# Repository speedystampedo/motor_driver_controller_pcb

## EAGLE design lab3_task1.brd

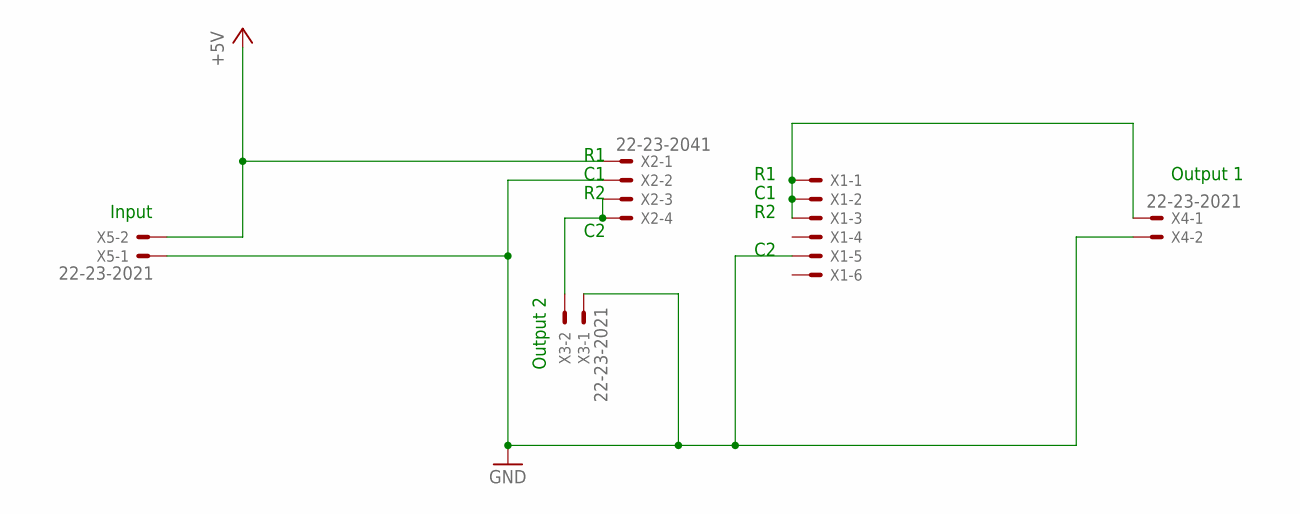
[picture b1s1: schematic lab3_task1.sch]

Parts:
X1: 22-23-2061
X2: 22-23-2041
X3, X4, X5: 22-23-2021

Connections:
+5V: X2.1, X5.2
GND: X1.5, X2.2, X3.1, X4.2, X5.1
unnamed: X1.1, X1.2, X1.3, X4.1
unnamed: X2.3, X2.4, X3.2

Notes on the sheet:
Output 1
Output 2
Input

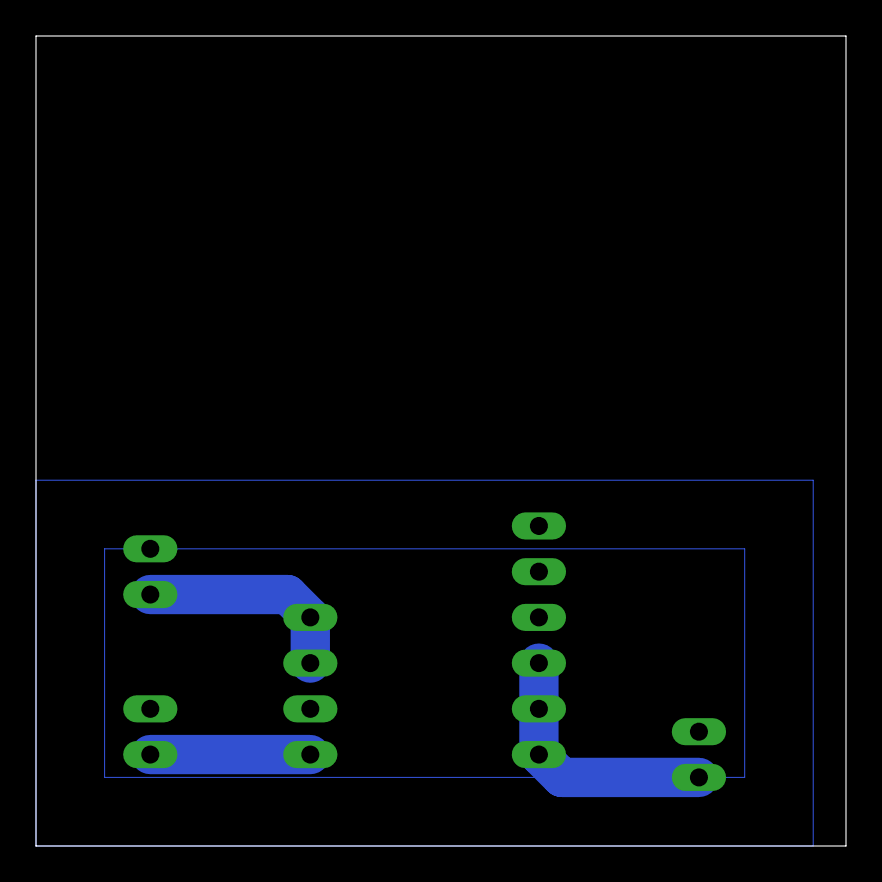
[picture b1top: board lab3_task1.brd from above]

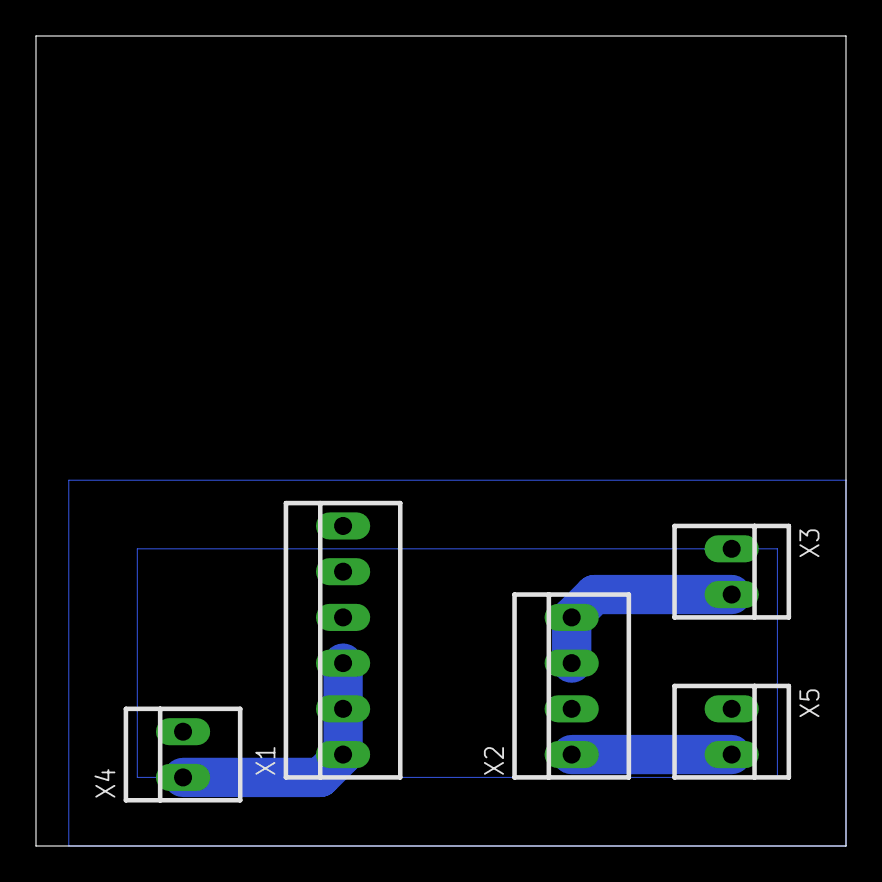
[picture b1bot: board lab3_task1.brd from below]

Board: 2 copper layers, 45.0 x 45.0 mm, 5 parts (5 on the bottom side), 4 nets.

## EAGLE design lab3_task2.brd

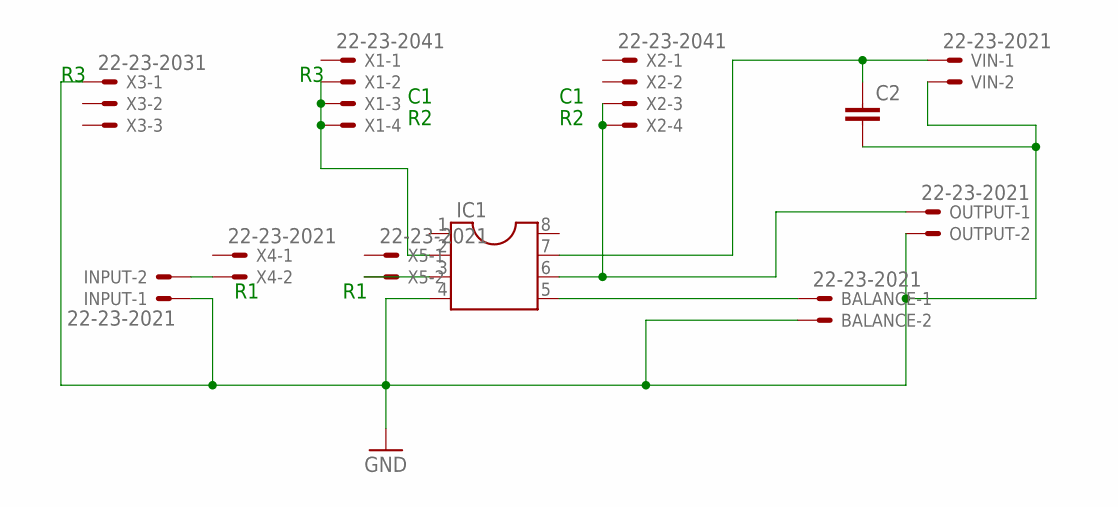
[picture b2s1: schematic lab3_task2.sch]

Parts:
BALANCE: 22-23-2021
C2: C-EU102-064X133; C102-064X133
IC1: DIL8; DIL08
INPUT: 22-23-2021
OUTPUT: 22-23-2021
VIN: 22-23-2021
X1, X2: 22-23-2041
X3: 22-23-2031
X4, X5: 22-23-2021

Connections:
GND: BALANCE.2, C2.2, IC1.4, INPUT.1, OUTPUT.2, VIN.2, X3.1
unnamed: INPUT.2, X4.2
unnamed: IC1.3, X5.2
unnamed: C2.1, IC1.7, VIN.1
unnamed: BALANCE.1, IC1.5
unnamed: IC1.6, OUTPUT.1, X2.3, X2.4
unnamed: IC1.2, X1.2, X1.3, X1.4

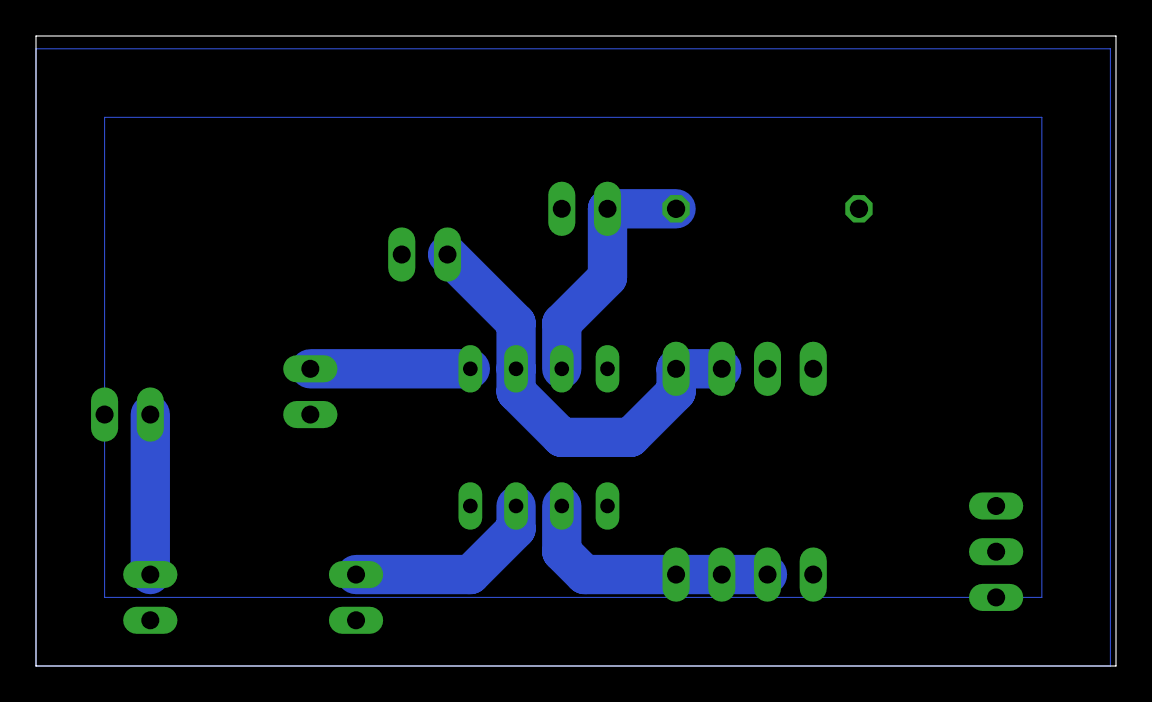
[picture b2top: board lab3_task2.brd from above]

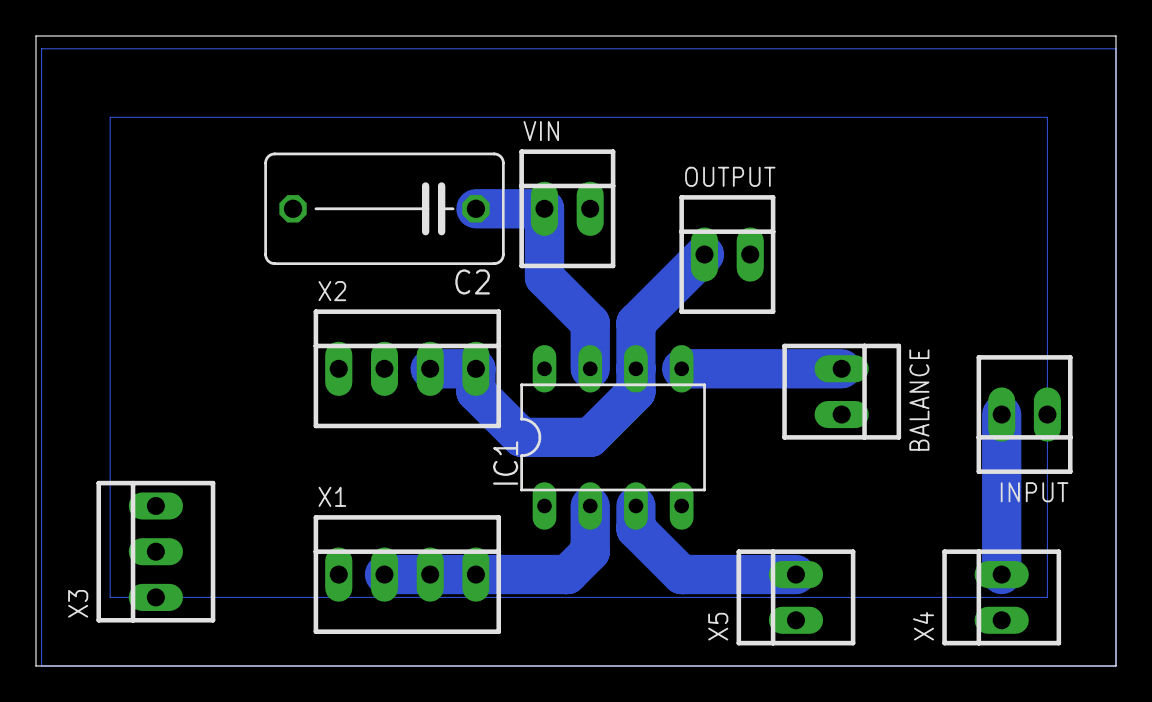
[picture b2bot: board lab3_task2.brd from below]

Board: 2 copper layers, 60.0 x 35.0 mm, 11 parts (11 on the bottom side), 7 nets.

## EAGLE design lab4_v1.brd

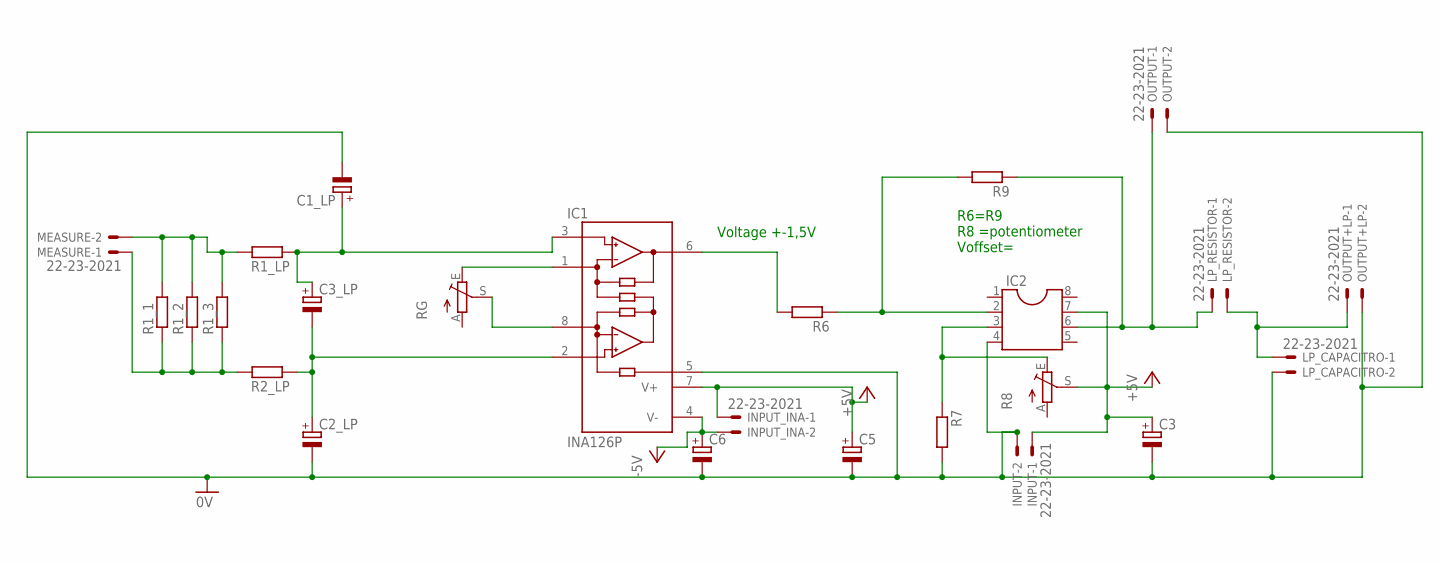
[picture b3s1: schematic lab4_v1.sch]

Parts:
C1_LP, C2_LP, C3, C3_LP, C5, C6: CPOL-EUE5-10.5; E5-10,5
IC1: INA126P; DIL08
IC2: DIL8; DIL08
INPUT: 22-23-2021
INPUT_INA: 22-23-2021
LP_CAPACITRO: 22-23-2021
LP_RESISTOR: 22-23-2021
MEASURE: 22-23-2021
OUTPUT: 22-23-2021
OUTPUT+LP: 22-23-2021
R1_1, R1_2, R1_3: R-EU_0617/22; 0617/22
R1_LP, R2_LP, R6, R7, R9: R-EU_0207/7; 0207/7
R8: TRIM_EU-B25P; B25P
RG: TRIM_EU-B25P; B25P

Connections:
+5V_1: C3.+, C5.+, IC1.7 (V+), IC2.7, INPUT.1, INPUT_INA.1, R8.S
-5V: C6.+, IC1.4 (V-), INPUT_INA.2
GND: C1_LP.-, C2_LP.-, C3.-, C5.-, C6.-, IC1.5 (REF), IC2.4, INPUT.2, LP_CAPACITRO.2, OUTPUT.2, OUTPUT+LP.2, R7.2
unnamed: C1_LP.+, C3_LP.+, IC1.3 (+IN), R1_LP.1
unnamed: C2_LP.+, C3_LP.-, IC1.2 (-IN), R2_LP.1
unnamed: IC1.8 (RG), RG.S
unnamed: IC1.1 (RG), RG.E
unnamed: IC1.6 (OUT), R6.2
unnamed: IC2.2, R6.1, R9.2
unnamed: IC2.3, R7.1, R8.E
unnamed: MEASURE.1, R1_1.1, R1_2.1, R1_3.1, R2_LP.2
unnamed: MEASURE.2, R1_1.2, R1_2.2, R1_3.2, R1_LP.2
unnamed: IC2.6, LP_RESISTOR.1, OUTPUT.1, R9.1
unnamed: LP_CAPACITRO.1, LP_RESISTOR.2, OUTPUT+LP.1

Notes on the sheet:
R6=R9 R8 =potentiometer Voffset=
Voltage +-1,5V

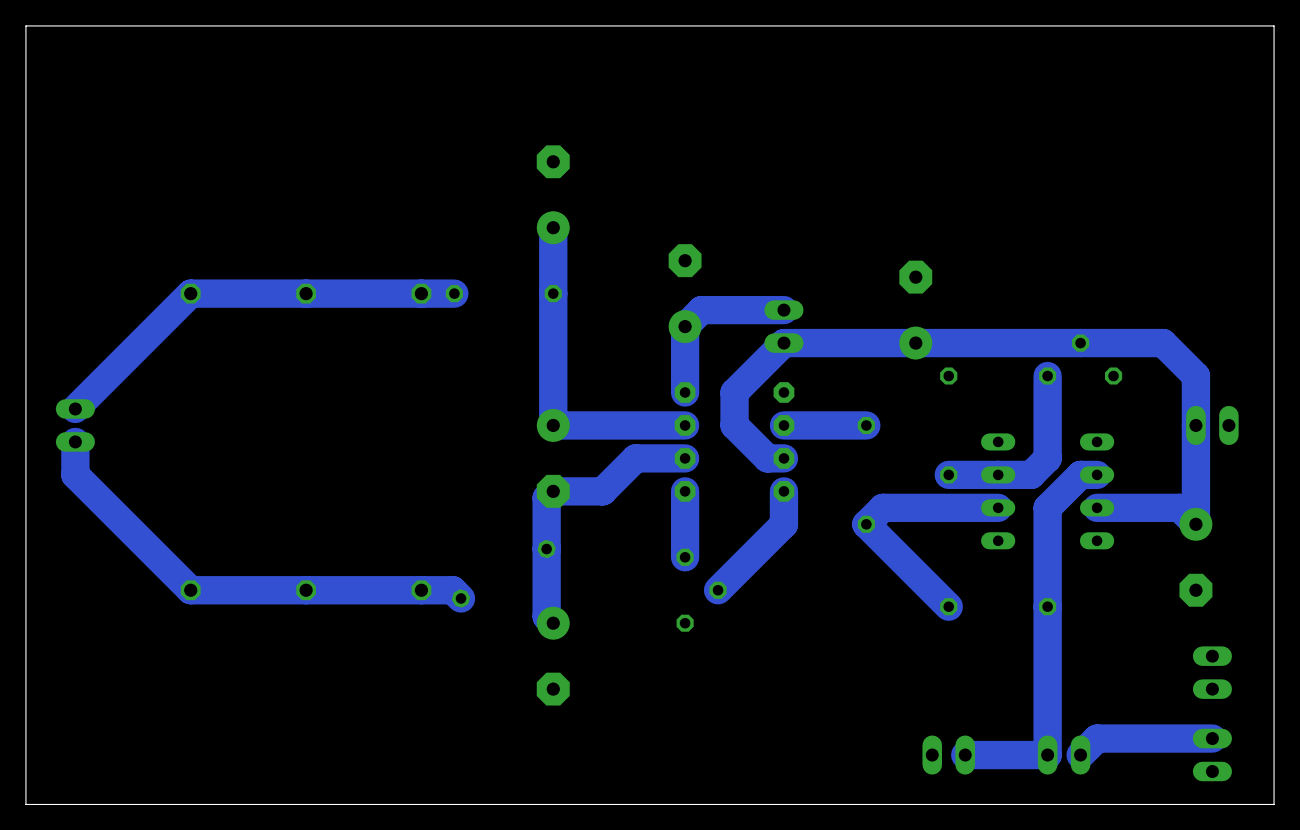
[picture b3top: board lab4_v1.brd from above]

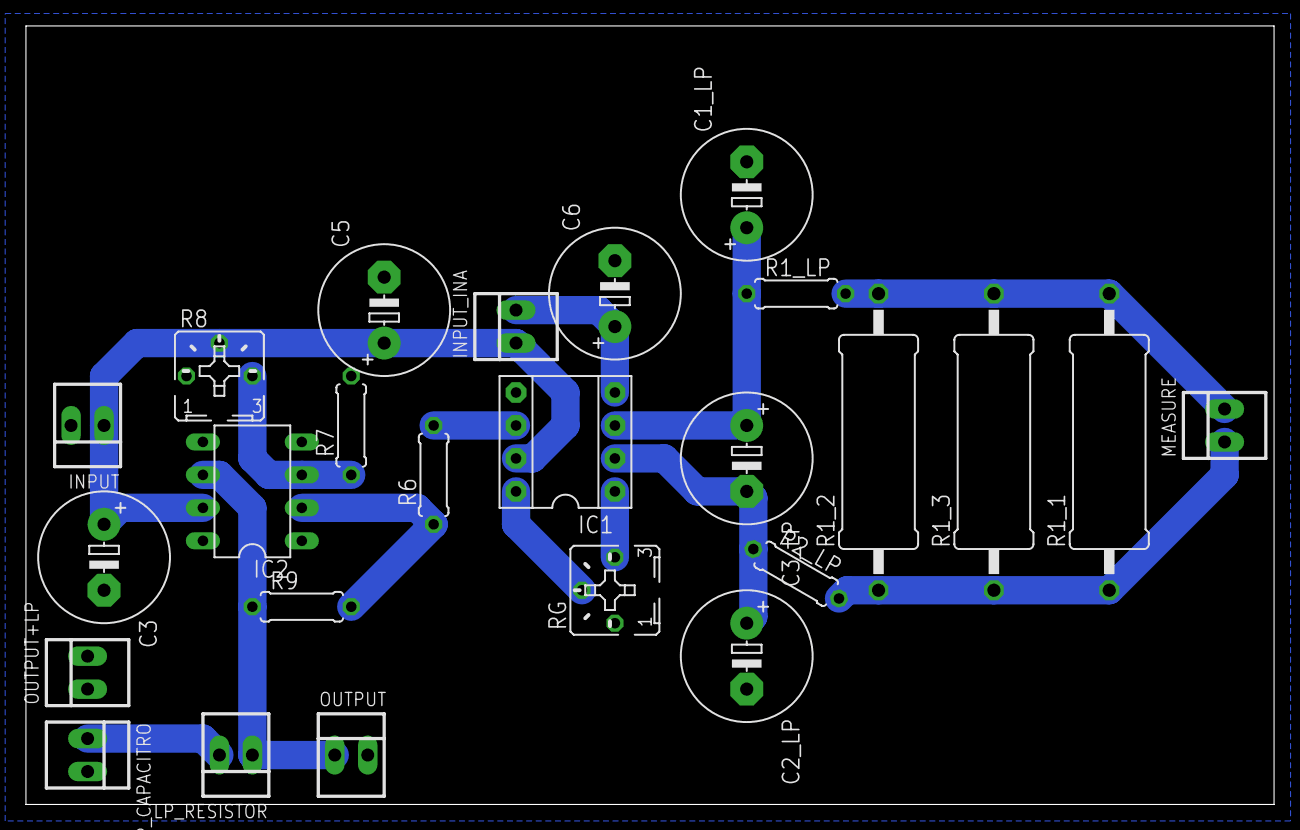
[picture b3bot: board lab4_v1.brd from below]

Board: 2 copper layers, 96.2 x 60.0 mm, 25 parts (25 on the bottom side), 14 nets.

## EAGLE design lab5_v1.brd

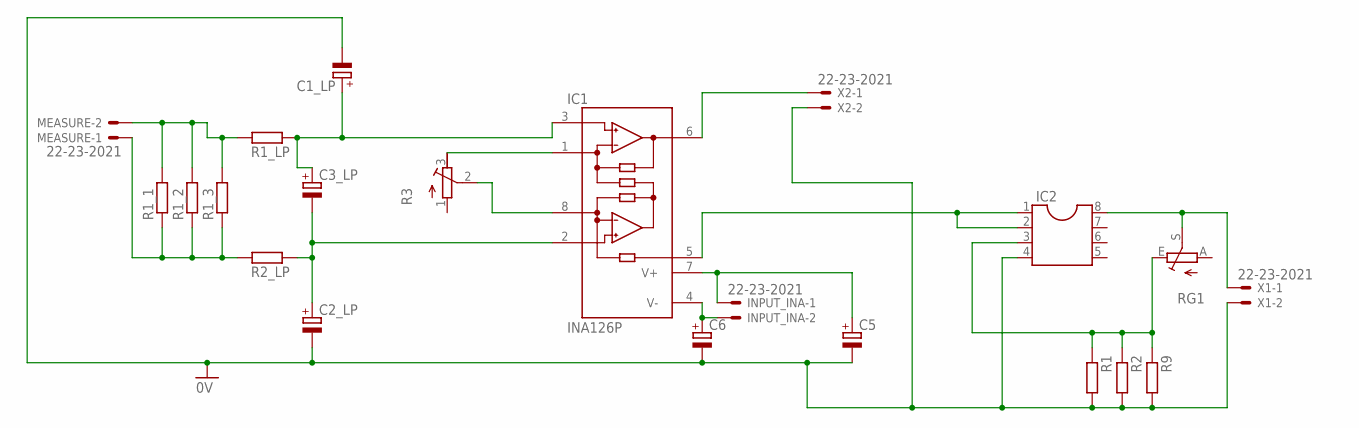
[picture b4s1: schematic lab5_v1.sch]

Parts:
C1_LP, C2_LP, C3_LP, C5, C6: CPOL-EUE5-10.5; E5-10,5
IC1: INA126P; DIL08
IC2: DIL8; DIL08
INPUT_INA: 22-23-2021
MEASURE: 22-23-2021
R1, R1_LP, R2, R2_LP, R9: R-EU_0207/7; 0207/7
R1_1, R1_2, R1_3: R-EU_0617/22; 0617/22
R3: R-TRIMM64X; RTRIM64X
RG1: TRIM_EU-B25P; B25P
X1, X2: 22-23-2021

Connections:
+5V_1: C5.+, IC1.7 (V+), INPUT_INA.1
GND: C1_LP.-, C2_LP.-, C5.-, C6.-, IC2.4, R1.2, R2.2, R9.2, X1.2, X2.2
unnamed: C1_LP.+, C3_LP.+, IC1.3 (+IN), R1_LP.1
unnamed: C2_LP.+, C3_LP.-, IC1.2 (-IN), R2_LP.1
unnamed: IC1.8 (RG), R3.2 (S)
unnamed: IC1.1 (RG), R3.3 (A)
unnamed: IC2.8, RG1.S, X1.1
unnamed: IC1.5 (REF), IC2.1, IC2.2
unnamed: IC2.3, R1.1, R2.1, R9.1, RG1.E
unnamed: MEASURE.1, R1_1.1, R1_2.1, R1_3.1, R2_LP.2
unnamed: MEASURE.2, R1_1.2, R1_2.2, R1_3.2, R1_LP.2
unnamed: IC1.6 (OUT), X2.1
unnamed: C6.+, IC1.4 (V-), INPUT_INA.2

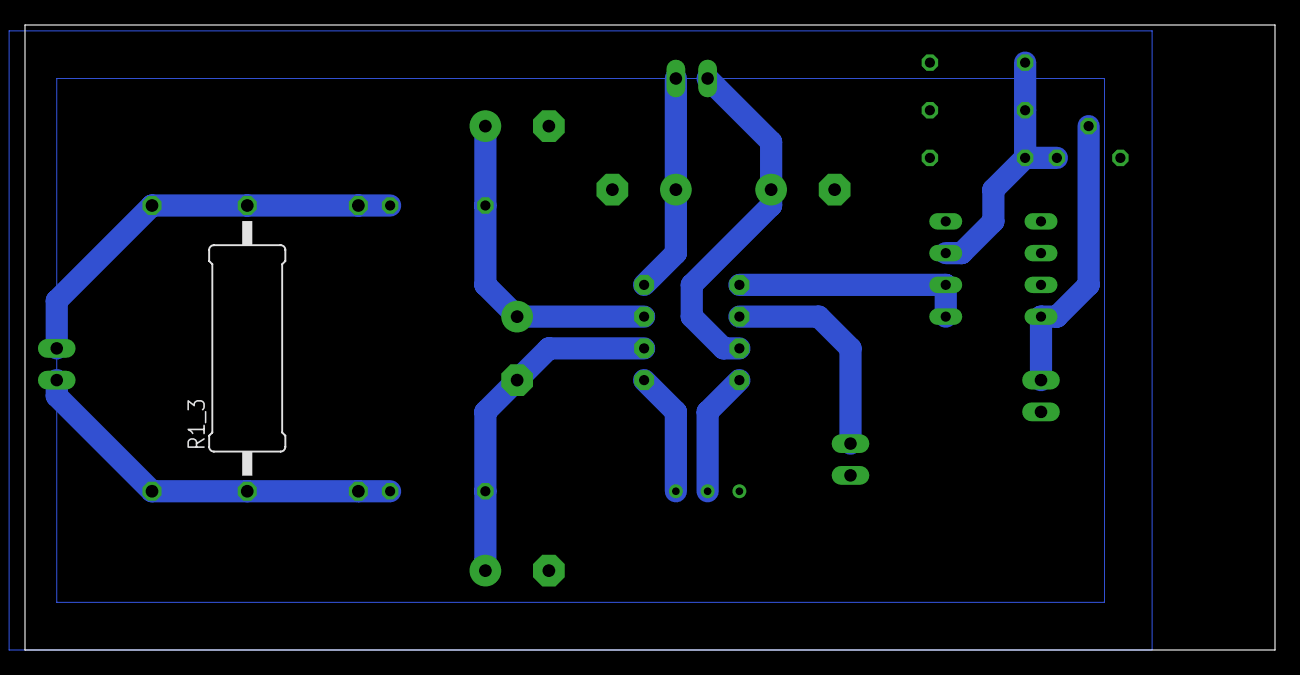
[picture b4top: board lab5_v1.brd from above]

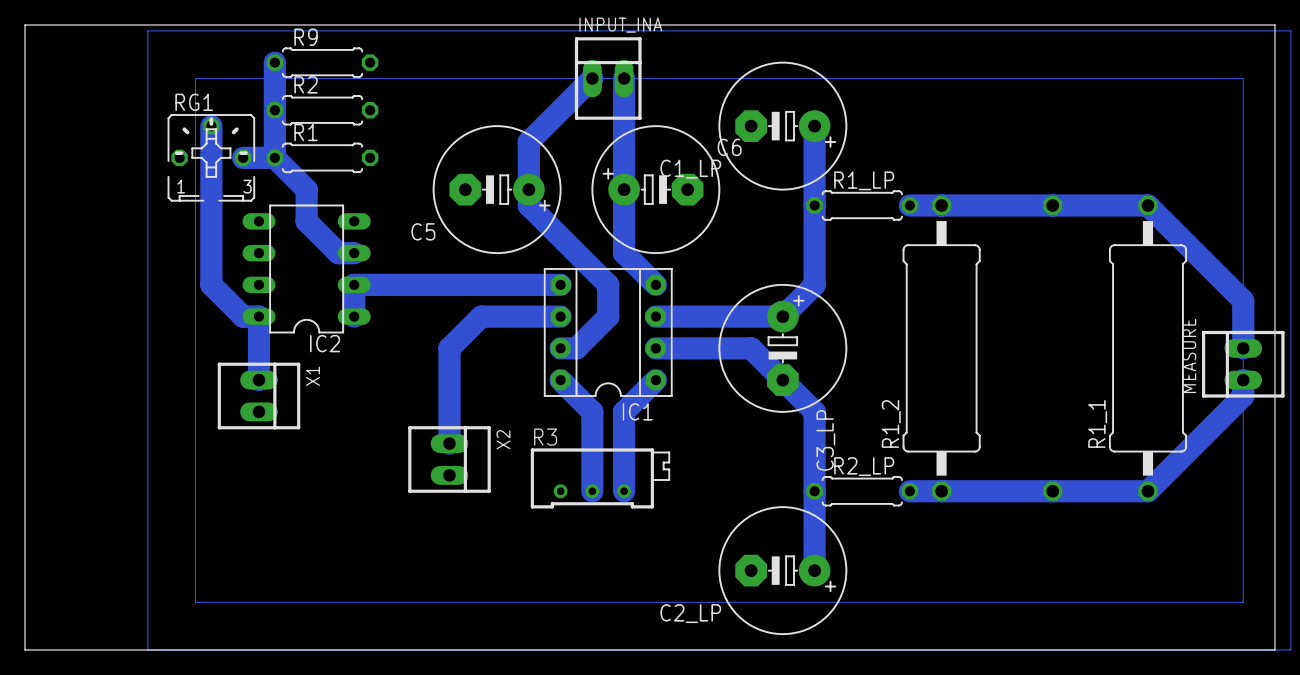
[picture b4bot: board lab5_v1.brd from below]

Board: 2 copper layers, 100.0 x 50.0 mm, 21 parts (20 on the bottom side), 13 nets.

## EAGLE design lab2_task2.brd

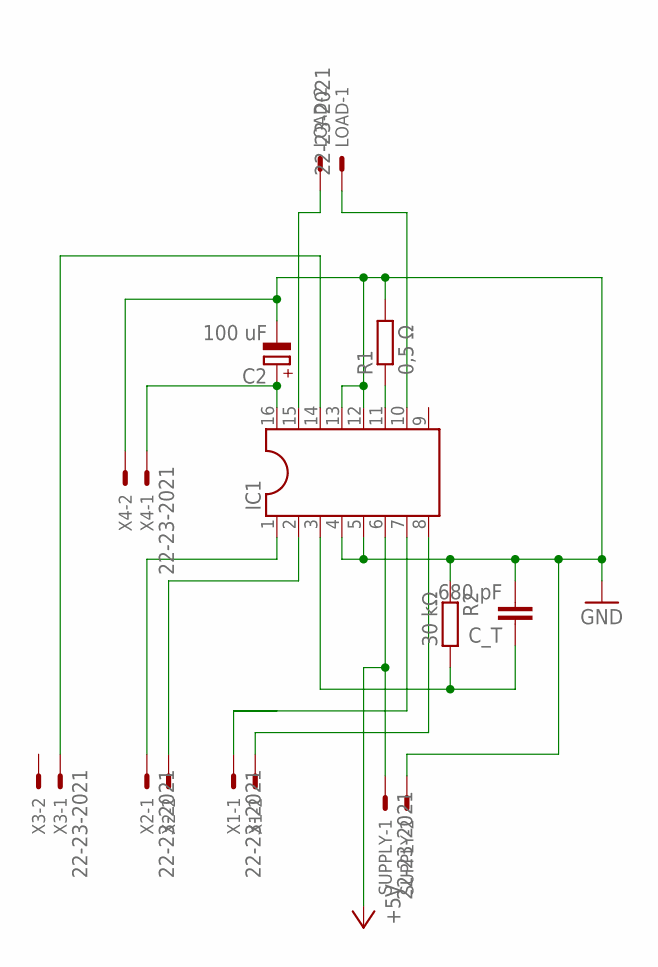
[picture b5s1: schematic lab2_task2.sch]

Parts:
C2: 100 uF; E5-13
C_T: 680 pF; C050-035X075
IC1: DIL16
LOAD: 22-23-2021
R1: 0,5 Ω; 0207/10
R2: 30 kΩ; 0207/10
SUPPLY: 22-23-2021
X1, X2, X3, X4: 22-23-2021

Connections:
+5V: IC1.6, SUPPLY.1
GND: C2.-, C_T.2, IC1.4, IC1.5, IC1.12, IC1.13, R1.2, R2.1, SUPPLY.2, X4.2
unnamed: IC1.7, X1.1
unnamed: IC1.8, X1.2
unnamed: C_T.1, IC1.3, R2.2
unnamed: C2.+, IC1.16, X4.1
unnamed: IC1.11, R1.1
unnamed: IC1.2, X2.2
unnamed: IC1.10, LOAD.1
unnamed: IC1.1, X2.1
unnamed: IC1.15, LOAD.2
unnamed: IC1.14, X3.1

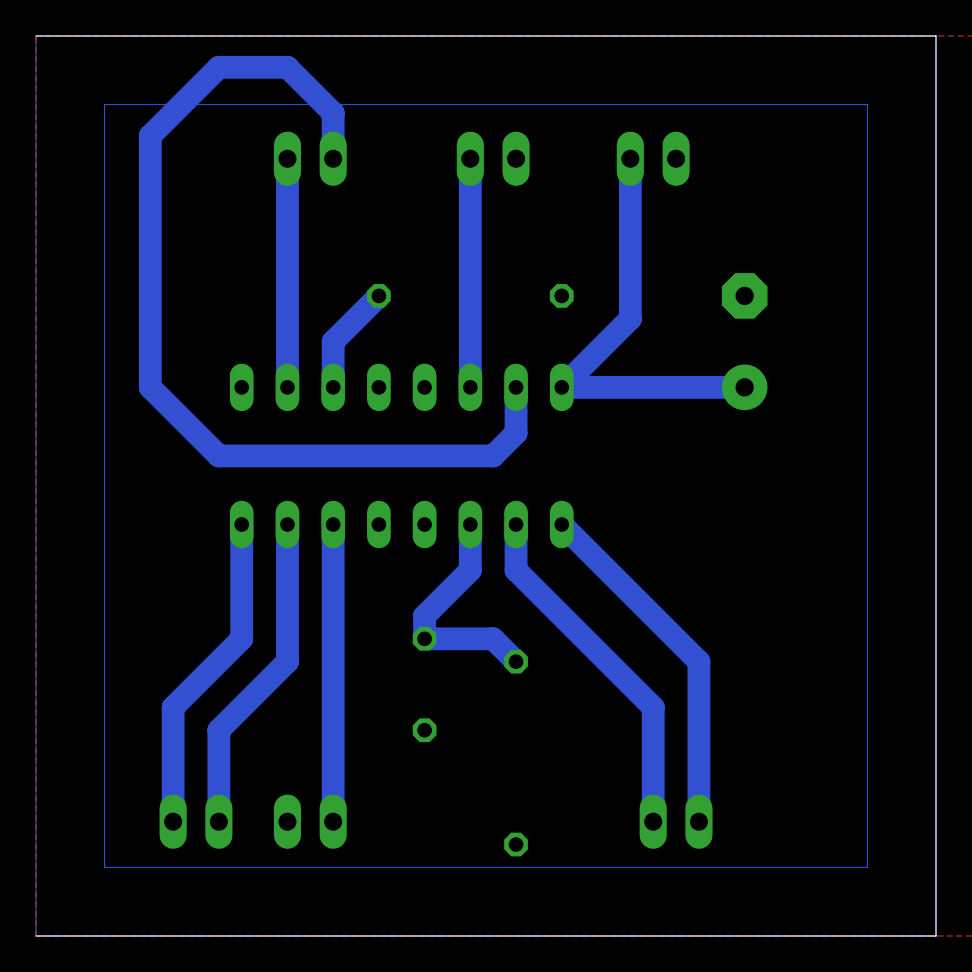
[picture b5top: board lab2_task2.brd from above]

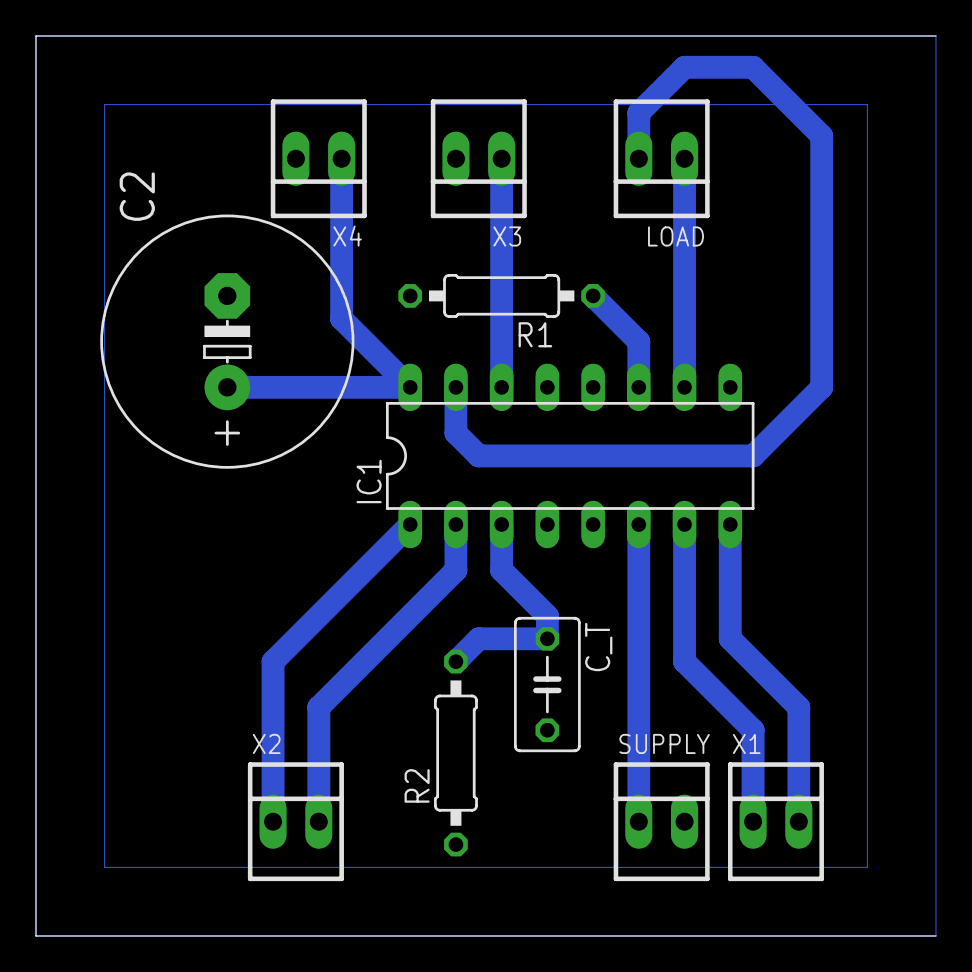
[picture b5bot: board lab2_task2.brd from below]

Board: 2 copper layers, 50.0 x 50.0 mm, 11 parts (11 on the bottom side), 12 nets.

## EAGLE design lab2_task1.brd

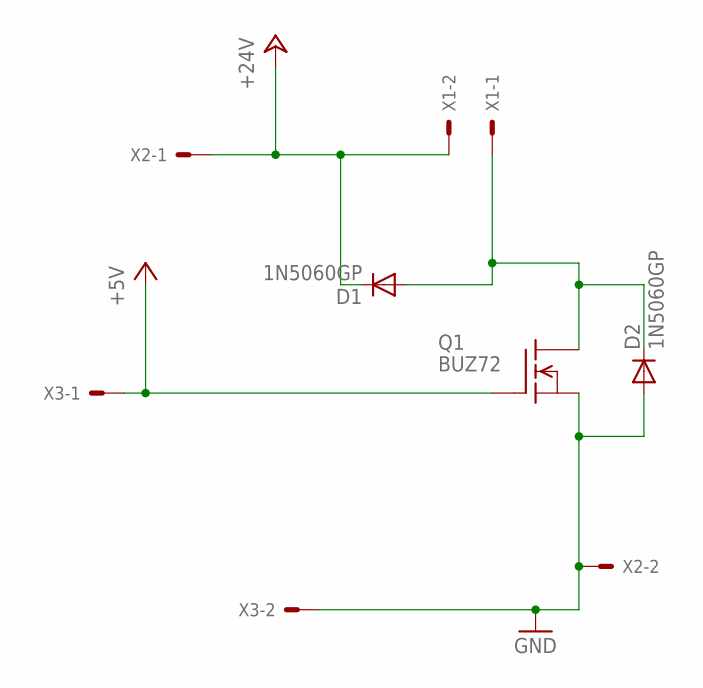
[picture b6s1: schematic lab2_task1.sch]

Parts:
D1, D2: 1N5060GP; DO15-12
Q1: BUZ72; TO220
X1, X2, X3: KK-156-2

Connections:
+5V: Q1.1 (G), X3.1
+24V: D1.C, X1.2, X2.1
GND: D2.A, Q1.3 (S), X2.2, X3.2
unnamed: D1.A, D2.C, Q1.2 (D), X1.1

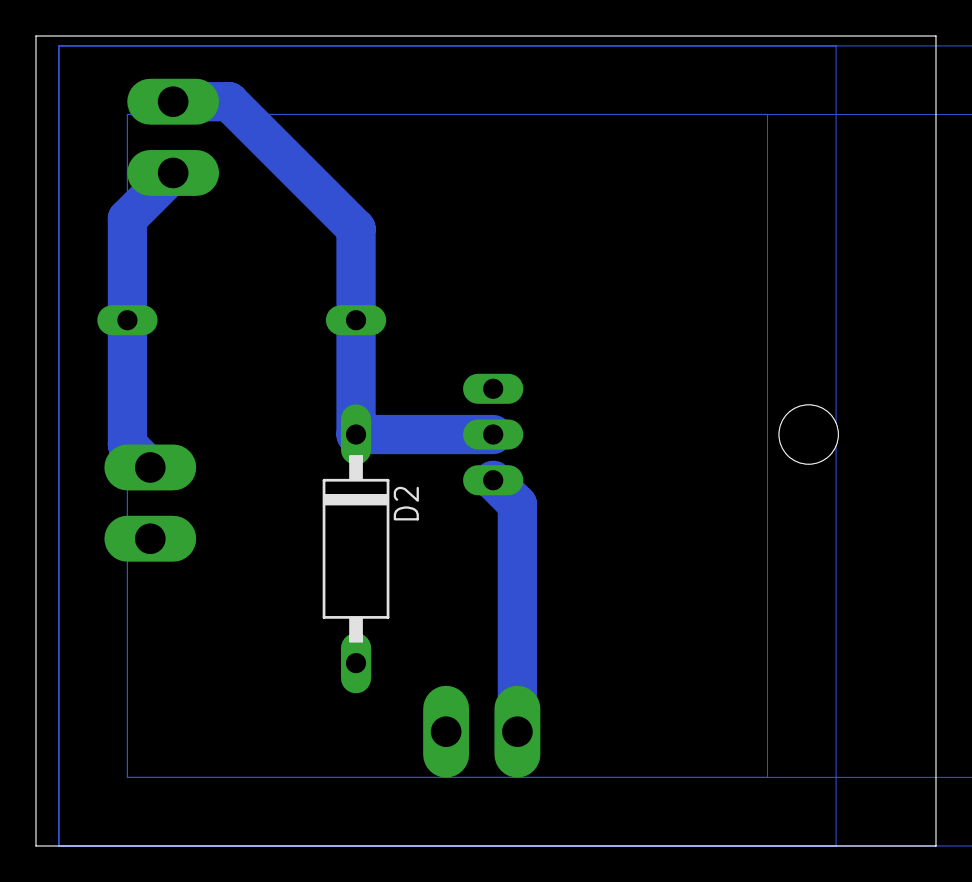
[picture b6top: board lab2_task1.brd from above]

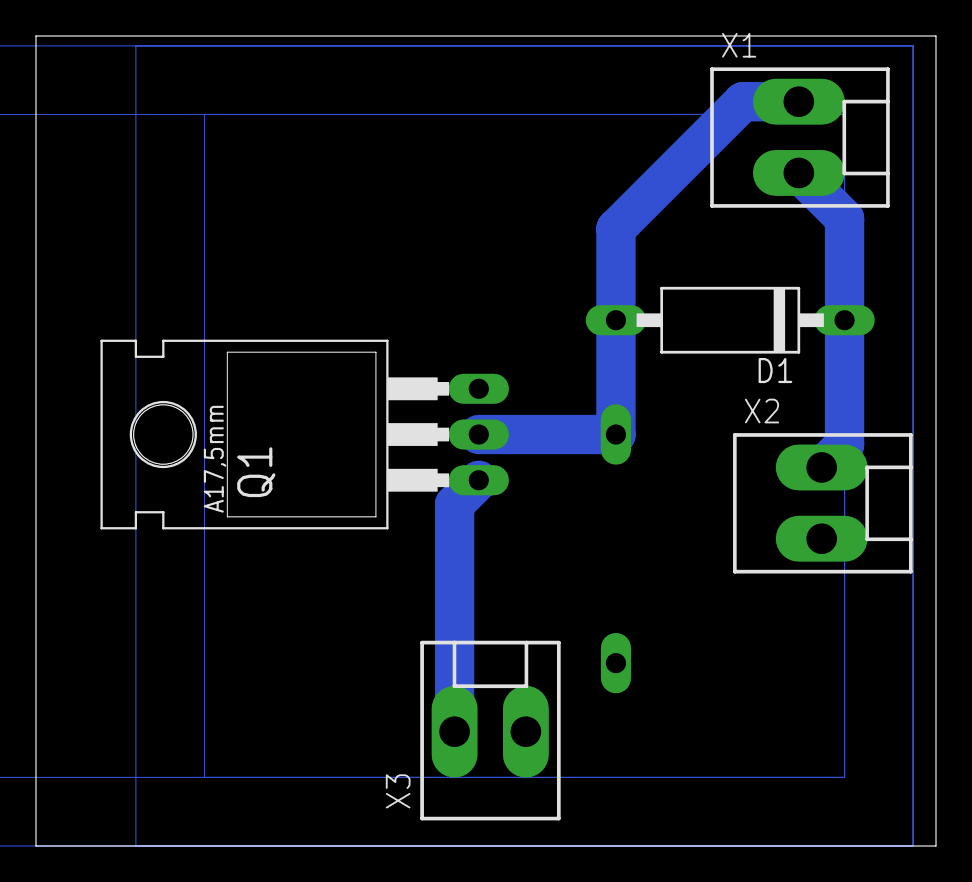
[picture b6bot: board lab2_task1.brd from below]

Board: 2 copper layers, 50.0 x 45.0 mm, 6 parts (5 on the bottom side), 4 nets.

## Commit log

2016-03-08 :neckbeard: Added .gitattributes & .gitignore files
